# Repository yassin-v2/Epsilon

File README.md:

# Epsilon

A very compact, 4-layer devboard integrating the RP2354A MCU, named Epsilon.

---

---

## Features

- **RP2354A MCU** - 32bit dual core ARM Cortex-M33 MCU, with RISC-V cores and 2Mb of internal flash memory.
- **Very compact, XIAO SEEED inspired formfactor**.
- **4 ADC and 7 digital GPIO pins**.
- **5V and 3.3V output power pins**.
- Power indicator LED and addressable LED.
- **USB C** - for programming and power.

---

## PCB Design

*Find the PCB files [here](https://github.com/yassin-v2/Epsilon/tree/main/PCB).*

The PCB is 4 layers with dimensions **21mm × 17.8mm**.

| Top Layer | Inner Plane 1; GND |
|:---------:|:------------:|
|  |  |

| Inner Plane 2; Power | Bottom Layer |
|:-----------:|:------------:|
|  |  |

---

## Schematic Design

*Find the Schematic files [here](https://github.com/yassin-v2/Epsilon/tree/main/PCB), or as a PDF, [here](https://github.com/yassin-v2/Epsilon/blob/main/Epsilon%20Schematic.pdf).*

---

## Pinout

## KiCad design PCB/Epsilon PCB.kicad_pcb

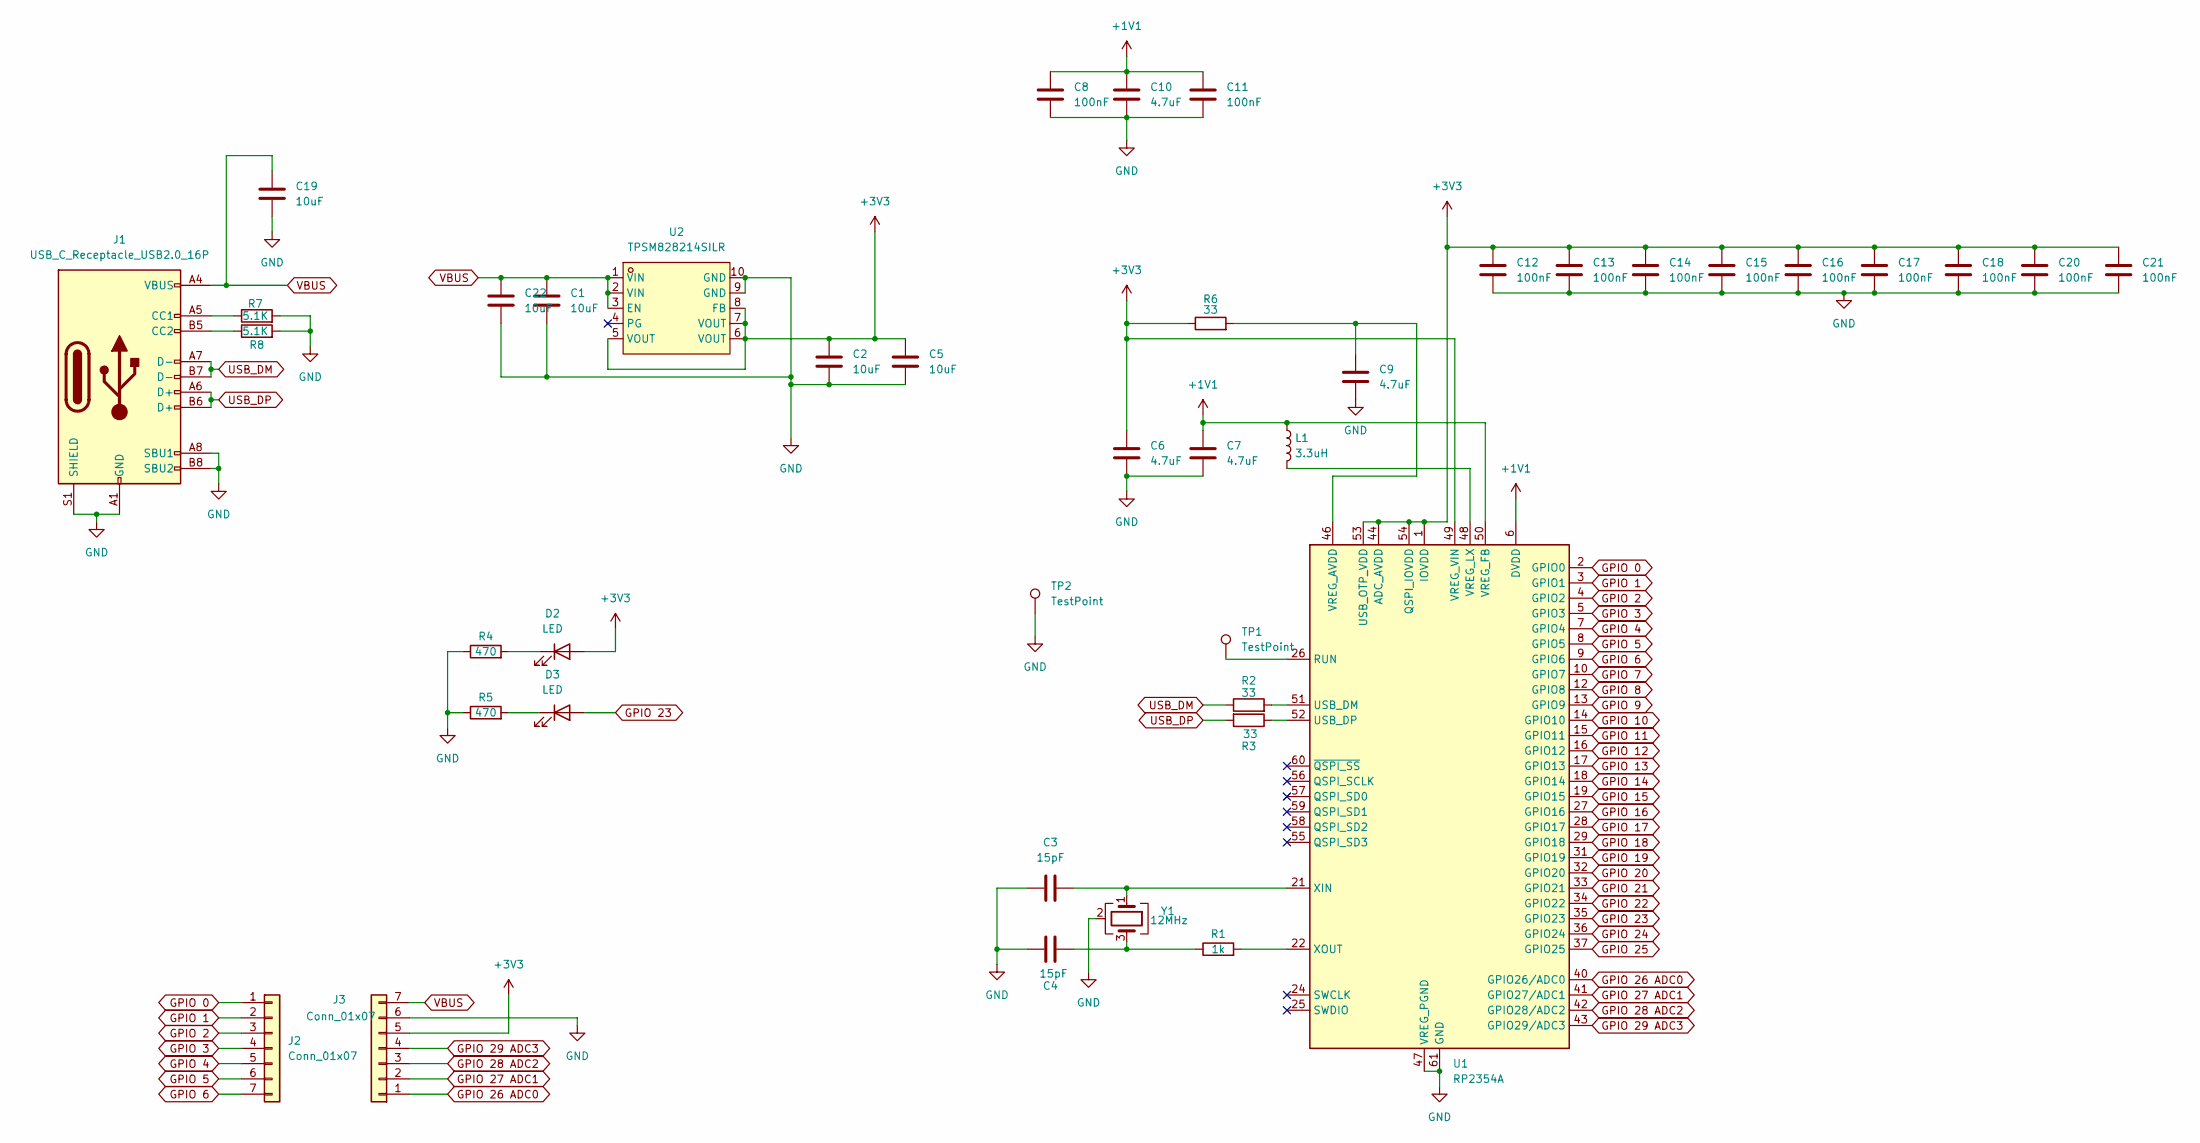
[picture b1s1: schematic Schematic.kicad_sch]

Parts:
C1, C2, C5, C19, C22: 10uF; C_0402_1005Metric
C3, C4: 15pF; C_0402_1005Metric
C6, C7, C9, C10: 4.7uF; C_0402_1005Metric
C8, C11, C12, C13, C14, C15, C16, C17, C18, C20, C21: 100nF; C_0402_1005Metric
D2, D3: LED; LED_0402_1005Metric
J1: USB_C_Receptacle_USB2.0_16P; USB_C_Receptacle_HRO_TYPE-C-31-M-12
J2, J3: Conn_01x07; PinHeader_1x07_P2.54mm_Vertical
L1: 3.3uH; IND-SMD_L2.0-W1.6_AOTA-B201610S3R3-101-T
R1: 1k; R_0402_1005Metric
R2, R3, R6: 33; R_0402_1005Metric
R4, R5: 470; R_0402_1005Metric
R7, R8: 5.1K; R_0402_1005Metric
TP1, TP2: TestPoint; TestPoint_Pad_1.0x1.0mm
U1: RP2354A; QFN-60-1EP_7x7mm_P0.4mm_EP3.4x3.4mm
U2: TPSM828214SILR; USIP-10_L2.5-W2.0-P0.50-BL; MPN TPSM828214SILR; LCSC Part C2876792
Y1: 12MHz; Crystal_SMD_Abracon_ABM8G-4Pin_3.2x2.5mm

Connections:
+1V1: C7.1, C8.1, C10.1, C11.1, L1.1, U1.6 (DVDD), U1.23 (DVDD), U1.39 (DVDD), U1.50 (VREG_FB)
+3V3: C2.1, C5.1, C6.1, C12.1, C13.1, C14.1, C15.1, C16.1, C17.1, C18.1, C20.1, C21.1, D2.2 (A), J3.5, R6.1, U1.1 (IOVDD), U1.11 (IOVDD), U1.20 (IOVDD), U1.30 (IOVDD), U1.38 (IOVDD), U1.44 (ADC_AVDD), U1.45 (IOVDD), U1.49 (VREG_VIN), U1.53 (USB_OTP_VDD), U1.54 (QSPI_IOVDD), U2.5 (VOUT), U2.6 (VOUT), U2.7 (VOUT), U2.8 (FB)
GND: C1.2, C2.2, C3.1, C4.1, C5.2, C6.2, C7.2, C8.2, C9.2, C10.2, C11.2, C12.2, C13.2, C14.2, C15.2, C16.2, C17.2, C18.2, C19.2, C20.2, C21.2, C22.2, J1.A1 (GND), J1.A8 (SBU1), J1.A12 (GND), J1.B1 (GND), J1.B8 (SBU2), J1.B12 (GND), J1.S1 (SHIELD), J3.6, R4.1, R5.1, R7.2, R8.2, TP2.1, U1.47 (VREG_PGND), U1.61 (GND), U2.9 (GND), U2.10 (GND), Y1.2 (G), Y1.4 (G)
GPIO 0: J2.1, U1.2 (GPIO0)
GPIO 1: J2.2, U1.3 (GPIO1)
GPIO 2: J2.3, U1.4 (GPIO2)
GPIO 3: J2.4, U1.5 (GPIO3)
GPIO 4: J2.5, U1.7 (GPIO4)
GPIO 5: J2.6, U1.8 (GPIO5)
GPIO 6: J2.7, U1.9 (GPIO6)
GPIO 7: U1.10 (GPIO7)
GPIO 8: U1.12 (GPIO8)
GPIO 9: U1.13 (GPIO9)
GPIO 10: U1.14 (GPIO10)
GPIO 11: U1.15 (GPIO11)
GPIO 12: U1.16 (GPIO12)
GPIO 13: U1.17 (GPIO13)
GPIO 14: U1.18 (GPIO14)
GPIO 15: U1.19 (GPIO15)
GPIO 16: U1.27 (GPIO16)
GPIO 17: U1.28 (GPIO17)
GPIO 18: U1.29 (GPIO18)
GPIO 19: U1.31 (GPIO19)
GPIO 20: U1.32 (GPIO20)
GPIO 21: U1.33 (GPIO21)
GPIO 22: U1.34 (GPIO22)
GPIO 23: D3.2 (A), U1.35 (GPIO23)
GPIO 24: U1.36 (GPIO24)
GPIO 25: U1.37 (GPIO25)
GPIO 26 ADC0: J3.1, U1.40 (GPIO26/ADC0)
GPIO 27 ADC1: J3.2, U1.41 (GPIO27/ADC1)
GPIO 28 ADC2: J3.3, U1.42 (GPIO28/ADC2)
GPIO 29 ADC3: J3.4, U1.43 (GPIO29/ADC3)
unnamed: C4.2, R1.1, Y1.3
unnamed: D2.1 (K), R4.2
unnamed: D3.1 (K), R5.2
unnamed: J1.A5 (CC1), R7.1
unnamed: J1.B5 (CC2), R8.1
unnamed: TP1.1, U1.26 (RUN)
unnamed: R2.2, U1.51 (USB_DM)
unnamed: R3.1, U1.52 (USB_DP)
unnamed: C9.1, R6.2, U1.46 (VREG_AVDD)
unnamed: L1.2, U1.48 (VREG_LX)
unnamed: C3.2, U1.21 (XIN), Y1.1
unnamed: R1.2, U1.22 (XOUT)
USB_DM: J1.A7 (D-), J1.B7 (D-), R2.1
USB_DP: J1.A6 (D+), J1.B6 (D+), R3.2
VBUS: C1.1, C19.1, C22.1, J1.A4 (VBUS), J1.A9 (VBUS), J1.B4 (VBUS), J1.B9 (VBUS), J3.7, U2.1 (VIN), U2.2 (VIN), U2.3 (EN)

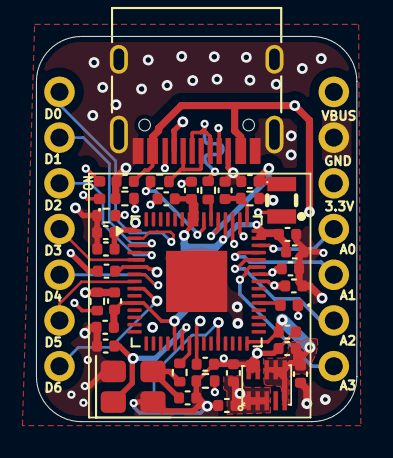
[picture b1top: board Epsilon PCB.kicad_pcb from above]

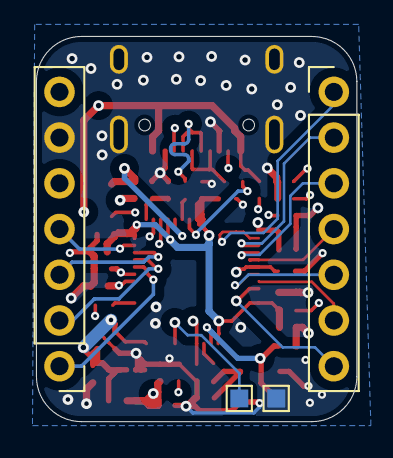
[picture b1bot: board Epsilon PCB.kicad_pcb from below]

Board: 4 copper layers, 17.8 x 21.4 mm, 41 parts (4 on the bottom side), 30 nets.

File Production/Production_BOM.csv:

Designator,Footprint,Quantity,Value,LCSC Part #
"C1, C19, C2, C22, C5",0402,5,10uF,
"C10, C6, C7, C9",0402,4,4.7uF,
"C11, C12, C13, C14, C15, C16, C17, C18, C20, C21, C8",0402,11,100nF,
"C3, C4",0402,2,15pF,
"D2, D3",0402,2,LED,
J1,USB_C_Receptacle_HRO_TYPE-C-31-M-12,1,USB_C_Receptacle_USB2.0_16P,
L1,IND-SMD_L2.0-W1.6_AOTA-B201610S3R3-101-T,1,3.3uH,C42411119
R1,0402,1,1k,
"R2, R3, R6",0402,3,33,
"R4, R5",0402,2,470,
"R7, R8",0402,2,5.1K,
U1,QFN-60-1EP_7x7mm_P0.4mm_EP3.4x3.4mm,1,RP2354A,
U2,USIP-10_L2.5-W2.0-P0.50-BL,1,TPSM828214SILR,C2876792
Y1,Crystal_SMD_Abracon_ABM8G-4Pin_3.2x2.5mm,1,12MHz,

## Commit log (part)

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2026-06-10 Uploaded files
2026-06-10 Change BOM.csv to use comma-separated values
2026-06-10 Added layer images
2026-06-10 README
2026-06-15 Readded PCB file with pro file
